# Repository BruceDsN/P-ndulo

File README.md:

Este repositorio contiene información de mi proyecto de péndulo invertido.
Podrás encontrar:
  1-Diseño de la PCB (Incluyendo librerías extras que utilicé)
  2-Código empleado
  3-Fotos y vídeos
                <3

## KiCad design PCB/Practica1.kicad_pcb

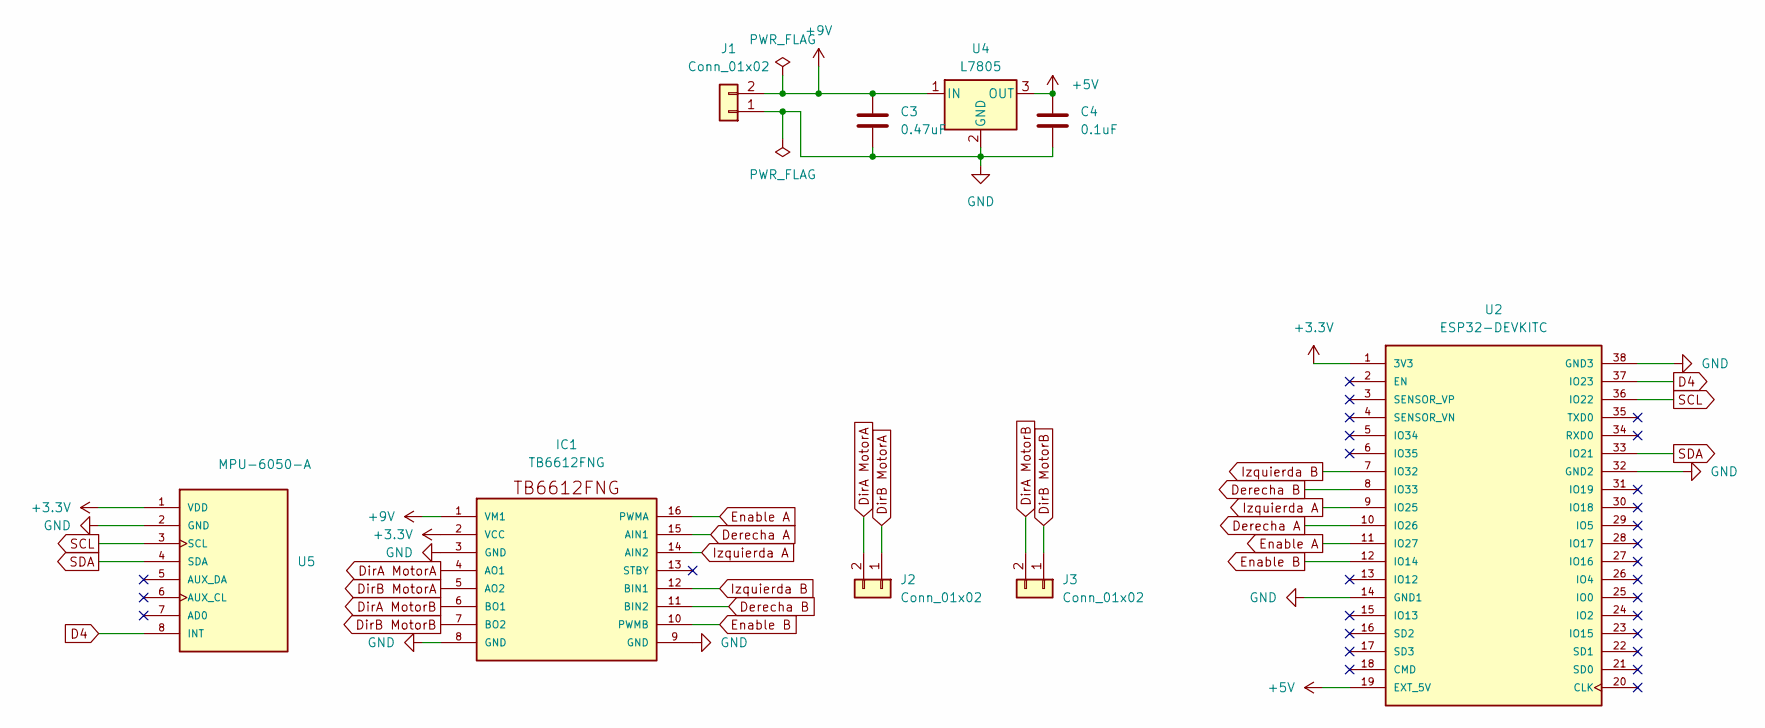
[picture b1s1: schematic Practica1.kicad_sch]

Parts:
C3: 0.47uF; CP_Radial_D8.0mm_P3.50mm
C4: 0.1uF; CP_Radial_D5.0mm_P2.00mm
IC1: TB6612FNG; TB6612FngSparkfun
J1, J2, J3: Conn_01x02; TerminalBlock_Phoenix_MKDS-1,5-2_1x02_P5.00mm_Horizontal
U2: ESP32-DEVKITC; MODULE_ESP32-DEVKITC; PARTREV N/A
U4: L7805; TO-220F-3_Vertical
U5: MPU-6050-A; MPU6050; PARTREV 3.4

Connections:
+3.3V: IC1.2 (VCC), U2.1 (3V3), U5.1 (VDD)
+5V: C4.1, U2.19 (EXT_5V), U4.3 (OUT)
+9V: C3.1, IC1.1 (VM1), J1.2, U4.1 (IN)
D4: U2.37 (IO23), U5.8 (INT)
Derecha A: IC1.15 (AIN1), U2.10 (IO26)
Derecha B: IC1.11 (BIN2), U2.8 (IO33)
DirA MotorA: IC1.4 (AO1), J2.2
DirA MotorB: IC1.6 (BO1), J3.2
DirB MotorA: IC1.5 (AO2), J2.1
DirB MotorB: IC1.7 (BO2), J3.1
Enable A: IC1.16 (PWMA), U2.11 (IO27)
Enable B: IC1.10 (PWMB), U2.12 (IO14)
GND: C3.2, C4.2, IC1.3 (GND), IC1.8 (GND), IC1.9 (GND), J1.1, U2.14 (GND1), U2.32 (GND2), U2.38 (GND3), U4.2 (GND), U5.2 (GND)
Izquierda A: IC1.14 (AIN2), U2.9 (IO25)
Izquierda B: IC1.12 (BIN1), U2.7 (IO32)
SCL: U2.36 (IO22), U5.3 (SCL)
SDA: U2.33 (IO21), U5.4 (SDA)

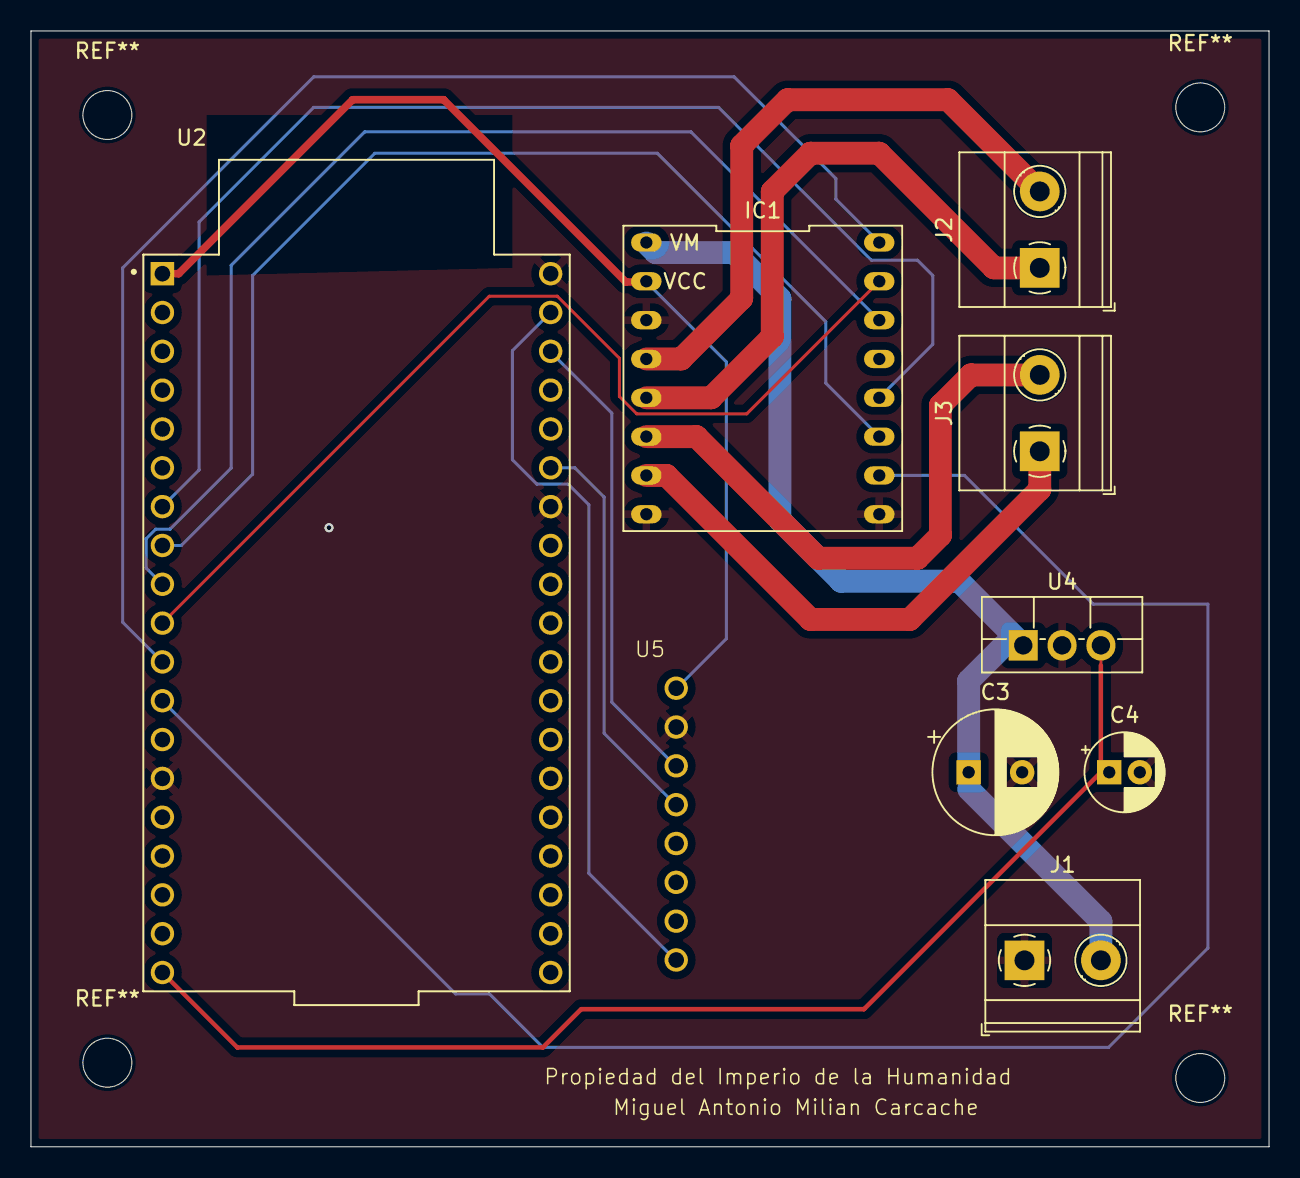
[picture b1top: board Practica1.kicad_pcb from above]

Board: 2 copper layers, 81.0 x 73.0 mm, 9 parts (0 on the bottom side), 17 nets.

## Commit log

2024-05-15 Pendulo
2024-05-15 Librerías
